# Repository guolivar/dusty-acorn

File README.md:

# DUSTY Air quality CORNer

Data parsing and visualisation for the Children's Air Quality Learning Corner. The data comes from a PACMAN (https://bitbucket.org/guolivar/pacman/wiki/Home) and it is converted to web pages aimed at children.

## Running the app locally

You will need the following tools installed in order to run this app

- Python 2.7+
- Tornado (`pip install tornado`)
- pySerial (`pip install pyserial`)

It has been developed and tested on a Ubuntu 14.04 with Chrome 46+, on a Mac OS 10 with Chrome 46+ and on a RPi Raspbian Jessie with Midori 0.5.11+

Once you have cloned the repository locally, fire your terminal in the project directory, and start the system with `python run.py`. You can browse the app in your browser using the URL `http://localhost:8080`.

Different web pages have been implemented to test different visualization methods:
* `http://localhost:8080/index.html` Basic "hello world" page showing the live feed from PACMAN as a table of values and as simple visualizations. Intended to illustrate the data and general visualization capabilities.
* `http://localhost:8080/bars.html` Vertical bars covering the screen, one for each sensor in different colours that reflect the measurements, taller bar means higher measurements.
The range of the bars is defined by the last 60 readings (max/min).
The distance sensor also controls the sounds emitted (think theremin).
* `http://localhost:8080/grid.html` The screen is divided in 4 sections dealing with specific sensors.
* `http://localhost:8080/temperature.html` The screen shows a single vertical bar scaled according to the last 60 readings (max/min) and if the max is reached, a chime plays.
* `http://localhost:8080/co2.html` The screen shows a single vertical bar scaled according to the last 60 readings (max/min) and if the max is reached, a chime plays.
* `http://localhost:8080/distance.html` The screen shows a single vertical bar scaled from 0 to ~60cm. The distance sensor also controls the sounds emitted (think theremin).
* `http://localhost:8080/dust.html` The screen shows a field of particles floating. The number of particles in the window is controlled by the readings of the dust sensor.
If the current reading is the max over the past 60 readings, a chime plays.

It will call the main method in the web_server.py script, which starts i) a Tornado web application with some handlers, a WebSocket server, two queues and a periodic callback (to check one of the queues), and ii) another "agent" thread.

The WebSocket server will communicate with the agent through its queues. One being for items to process, and other with responses. The response always contains a heartbeat object, which is a dictionary with various metrics to be displayed in the UI.

This app is based on tracker, another tool written in NIWA to monitor a device that controls hardware that tracks the sun, deployed in Lauder/NZ and Antarctica.

## Configurations

The bind address by default is set to `0.0.0.0` in the web_server.py file.

The port is set to `8080` in the web_server.py file.

The WebSocket URL used by the JavaScript code to connect to the server defaults to `ws://localhost:8080` and is defined in `templates/index.html`. You may need to change this address, in case you are trying to allow remote users to use your app.

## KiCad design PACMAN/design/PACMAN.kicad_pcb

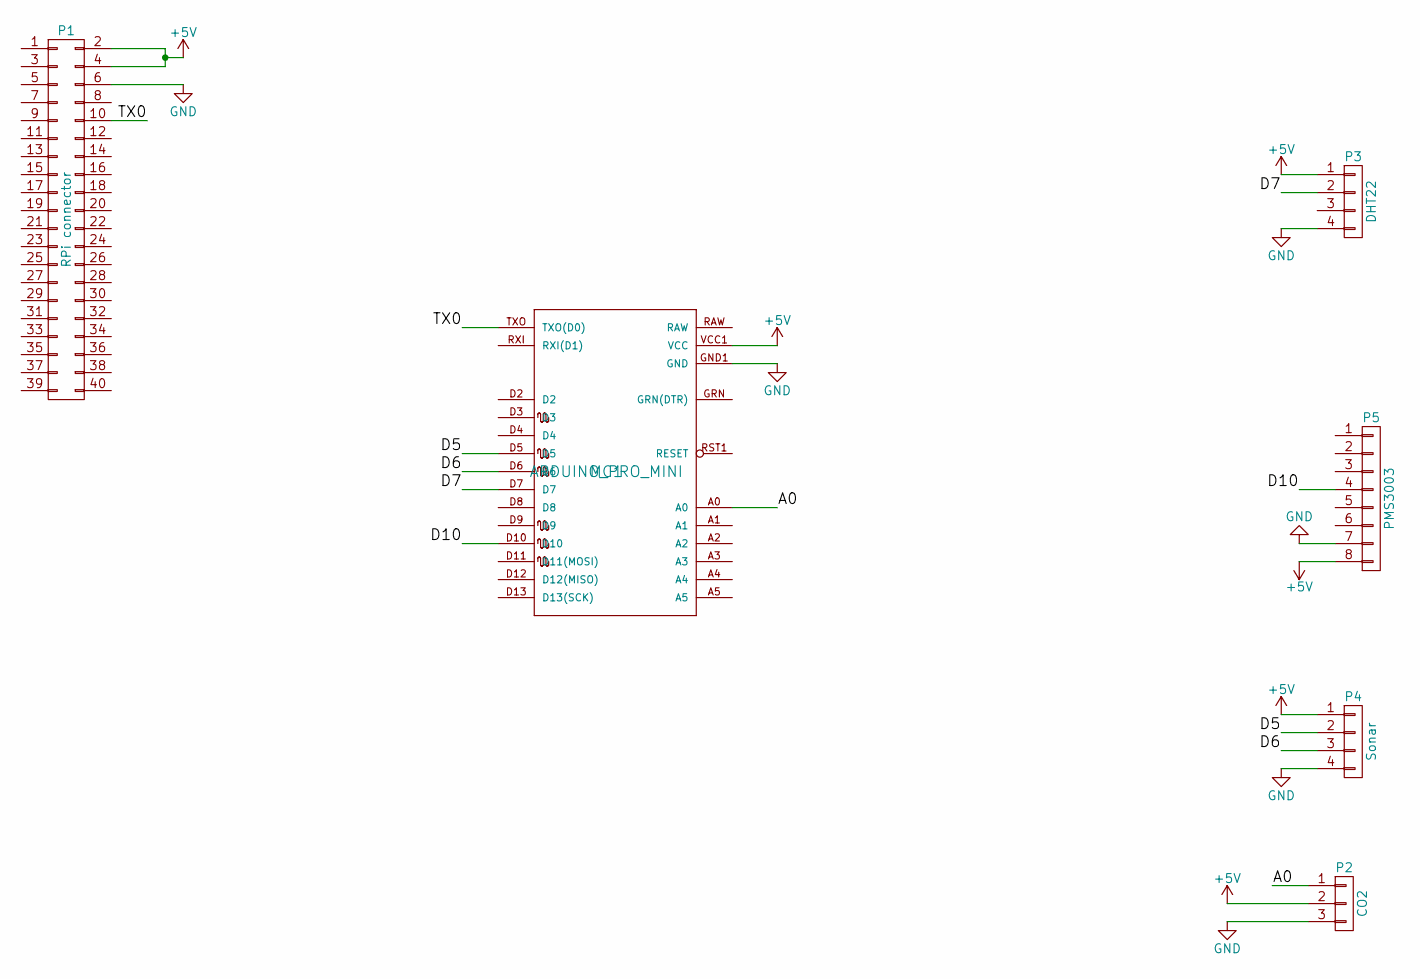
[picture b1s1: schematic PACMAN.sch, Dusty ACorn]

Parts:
MC1: ARDUINO_PRO_MINI; Halley-ARDUINO_PRO_MINI
P1: RPi connector; Pin_Header_Straight_2x20
P2: CO2; Pin_Header_Straight_1x03
P3: DHT22; Pin_Header_Straight_1x04
P4: Sonar; Pin_Header_Straight_1x04
P5: PMS3003; Pin_Header_Straight_1x08

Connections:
+5V: MC1.VCC1 (VCC), P1.2, P1.4, P2.2, P3.1, P4.1, P5.8
/A0: MC1.A0, P2.1
/D5: MC1.D5, P4.2
/D6: MC1.D6, P4.3
/D7: MC1.D7, P3.2
/D10: MC1.D10, P5.4
/TX0: MC1.TXO (TXO(D0)), P1.10
GND: MC1.GND1 (GND), P1.6, P2.3, P3.4, P4.4, P5.7

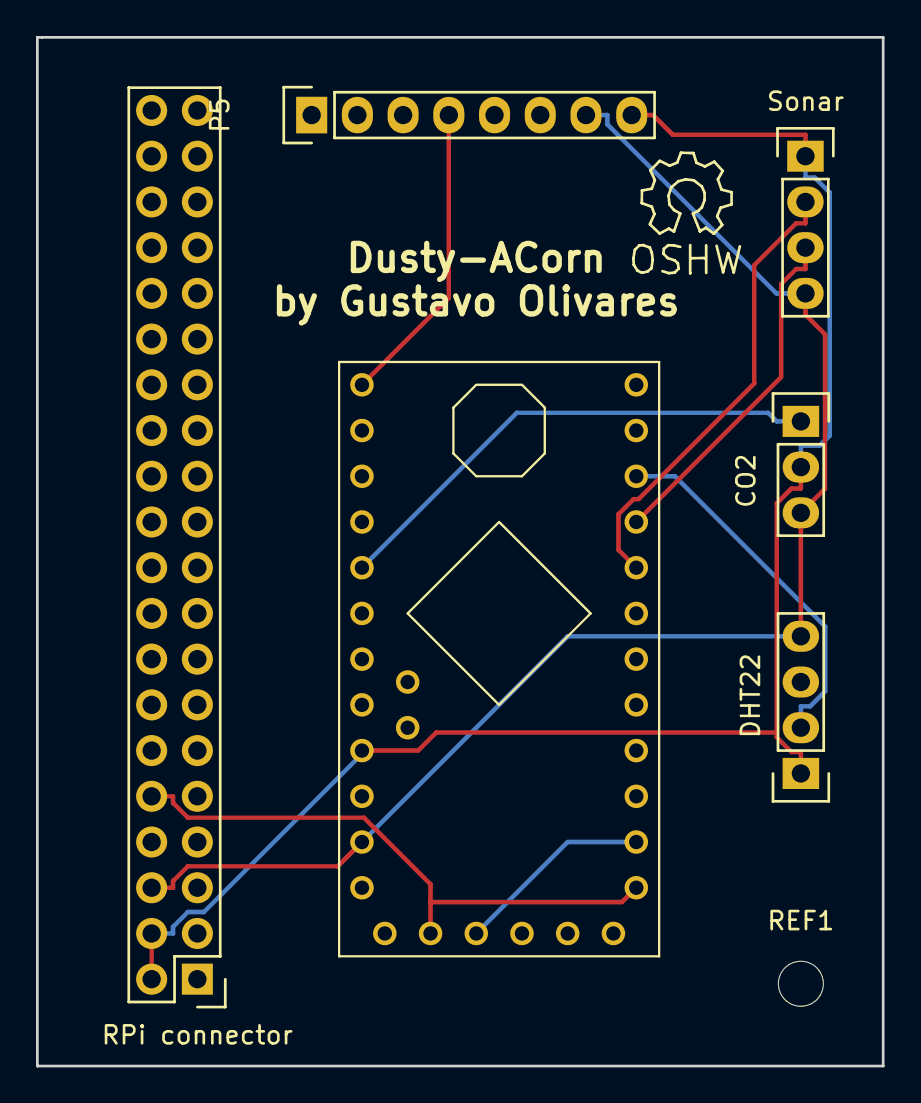
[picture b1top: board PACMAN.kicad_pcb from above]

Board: 2 copper layers, 47.0 x 57.2 mm, 8 parts (0 on the bottom side), 8 nets.

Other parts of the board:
REF1: MountingHole_2-5mm
REF2: Symbol_OSHW-Logo_SilkScreen

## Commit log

2015-10-27 Adjust gitignore
2015-10-27 Remove internal IP addresses
2015-10-27 Updating readme with running instructions
2015-10-27 Added config file to hold serial port data Added "real pacman" data fetch
2015-10-28 Update the agent to look for the real PACMAN Fix "non numeric character in the serial line" bug Hopefully
    TODO:
    use config file to choose real/test PACMAN data
2015-10-29 Modified config file to switch between test and live Removed "FakePacman" and made "Pacman" aware of the test/live switch in the config file Fixed wrong indices in the "index.html" template.
2015-10-29 Update README.md
    Updated readme with pySerial and mention of the Raspberry Pi tests
2015-11-03 Added serial debugging messages.
2015-11-04 Implemented screensaver turn off (requires xscreensaver). Started sound implementation (using pygame.midi)
2015-11-05 Sound parts run without errors ... if there is a midi server running.
2015-11-05 Changed approach to sound. No MIDI requirement. Now using "mpg123" to play specific mp3 files depending on the distance measured
2015-11-05 Added sound files
2015-11-05 Added Kdevelop4 files
2015-11-09 Testing two new views
2015-11-10 Removed FakePacman class as the config.txt file deals with live/test setup.
2015-11-10 Extended the range of notes and tweaked the range finder. Also changed the dust density to a cubic scale to make differences more visible.
2015-11-11 Changed the temperature output to only use the external one. Removed reference to FakePacman in agent.py Removed end-of-line character building as it is not needed (using getline method instead)
2015-11-11 Rolled back dealing with CO data
2015-11-11 Comment out of place ... removing the parsing of the data!
2015-11-11 Updated colours in bars.html Added distance column to bars.html Reduced the waiting time for the agent to try to minimise serial port buffering Added temporary fix to motion sensor.
2015-11-11 screensaver tweaks
2015-11-11 I had messed up the colours
2015-11-12 Some tweaks: CO2 is now inverted ... closer to real CO2 signal movement is taken from PACMAN but screensaver control is overridden Added camera view to bars.html
2015-11-12 Updated readme and added debug message to STDIO
2015-11-16 Create gh-pages branch via GitHub
2015-11-16 Messing about
2015-11-17 Added an image
2015-11-17 I missed an edit
2015-11-24 Changed sound feedback to web-pages Moved sound files to standard location Removed header from pacman sample Added "length of line" check in pacman.py parse-data
2015-11-25 Working pages for CO2, distance, temperature and dust. Added a chime sound when the maximum of the bar is updated Updated README file
2015-11-25 Added "maximum reached" sound.
2015-11-25 Fixed bug with the max/min calculations for temperature
2015-11-25 BugFix: webserver wasn't listening when only loopback was available. Replaced '0.0.0.0' with '127.0.0.1' in the server settings Signed-off-by: Gustavo Olivares <guolivar@gmail.com>
2015-11-25 Changed references to `localhost` to `127.0.0.1` for off-line use
2016-04-13 Included custom firmware for PACMAN board. -SD card not required for DustyACorn. PACMAN ignores SD card errors. -RTC not required for DustyACorn. PACMAN uses fallback internal counter for timing.
2016-05-03 faster refresh rate for the web pages
2016-05-03 Added original electrical designs from PACMAN v5
2016-05-24 Preparing to add PMS3003 support and updates to sensors
2016-05-25 Working with the distance sensor now.
2016-05-25 Apparently now it's working for the new version
2016-05-25 Removing the ATtiny code
2016-07-06 New Home page. Updated PACMAN firmware. Updated data parsing.
2016-07-11 New data line working
2016-07-15 Updated pages
2016-08-10 Raspberry Pi B+ hat for Dusty-ACorn ready for manufacture
2016-08-18 Unexpected closed socket solved
2016-08-18 Working demo!
2016-08-19 Merging work at work to prepare deployment
2016-08-20 It lives!
2016-10-03 Changed specific visualizations and added nav bar to main page
2016-10-03 Updated Arduino firmware
2016-10-04 Improved nav bar and visualisation panes
2016-10-25 Tidying up the firmware ... fewer variables.
2016-10-25 Removed viewport tag from bars visualisation
2016-10-25 Tweaking size of bars for bars.html visualisation (trying to fit to target device)
2016-10-25 Another try with the sizes
2016-10-25 Hopefully this solves the scrolling issue
2016-10-25 Applied same tweak to CO2 and Temperature pages
2016-10-25 Widget bar width to 215
2016-10-25 Fixed order of columns and colours matching the box
2016-10-25 final tweak of colours
2016-10-25 Now with added logging!
2016-10-25 Bug on writing ... programme didn't know where to save
2016-10-25 self self self ... 100 times self
2017-08-10 Fixed bug with the T&RH sensor and re-scale of the RH display
2017-08-10 Fixed bug with Range Finder (swapped trigger and echo pins)
2017-08-17 Set theme jekyll-theme-cayman and migrate Page Generator content
2017-08-17 Set theme jekyll-theme-cayman
2017-08-18 Rename LICENSE to LICENSE.txt
2017-08-19 Add requirements.txt file
2017-08-19 Make the project Python3 compatible
2019-03-05 Faster PACMAN operation
2019-04-16 Add new top level package for dusty_acorn module
2019-04-16 Add back air1.web_server as dusty_acorn.main
2019-04-16 Move static and templates under new package
2019-04-16 Remove old requirements file
2019-04-16 Add setup.py with requirements and other utilities
2019-04-16 Re-format agents.py code
2019-04-16 Re-format main.py code
2019-04-16 Adding back air1.pacman as dusty_acorn.pacman
2019-04-16 Include non-py files in the final package too
2019-04-16 Simplify dictionary creation
2019-04-16 Remove IDE files
2019-04-16 Re-format pacman.py code
2019-04-16 Adding back static folder
2019-04-16 Remove package __init__ file
2019-04-16 Remove old files
2019-04-16 air1.agent is now dusty_acorn.agents
2019-04-16 Add docstrings and rename parameters
2019-04-16 Add a group for the pygame testing script
2019-04-16 Remove run.py, use setuptools +venv now instead
2019-04-16 Add main method
2019-04-16 Close iframe tag
2019-04-16 Remove duplicate close tag for body
2019-04-16 Add missing semicolon (old ES)
2019-04-16 Compare with === instead of ==
2019-04-16 Re-format testing_sounds.py
2019-04-16 Replace hash comments by multiline comments
2019-04-16 0% percent is redundant
2019-04-16 Typo in themomether
2019-04-16 Avoid instantiating unnecessary variables
2019-04-16 Declare key variable in for-loop
2019-04-16 Remove invalid width and height
2019-04-16 Remove script not found in directory
2019-04-16 Absolute imports (main method)
2019-04-16 Add parameters via click, and add dependency in setup.py
2019-04-16 Output data in a tabular way
2019-04-16 Add versions and ranges
2019-09-05 Start work on ESP32 based v2019
2019-09-05 Bare bones ESP32 based ... not fully tested
2019-09-05 All done except range finder. Dust: OK T&RH: OK CO2: OK HC-SR04: FAIL
2019-09-05 Removed Serial verbosity
